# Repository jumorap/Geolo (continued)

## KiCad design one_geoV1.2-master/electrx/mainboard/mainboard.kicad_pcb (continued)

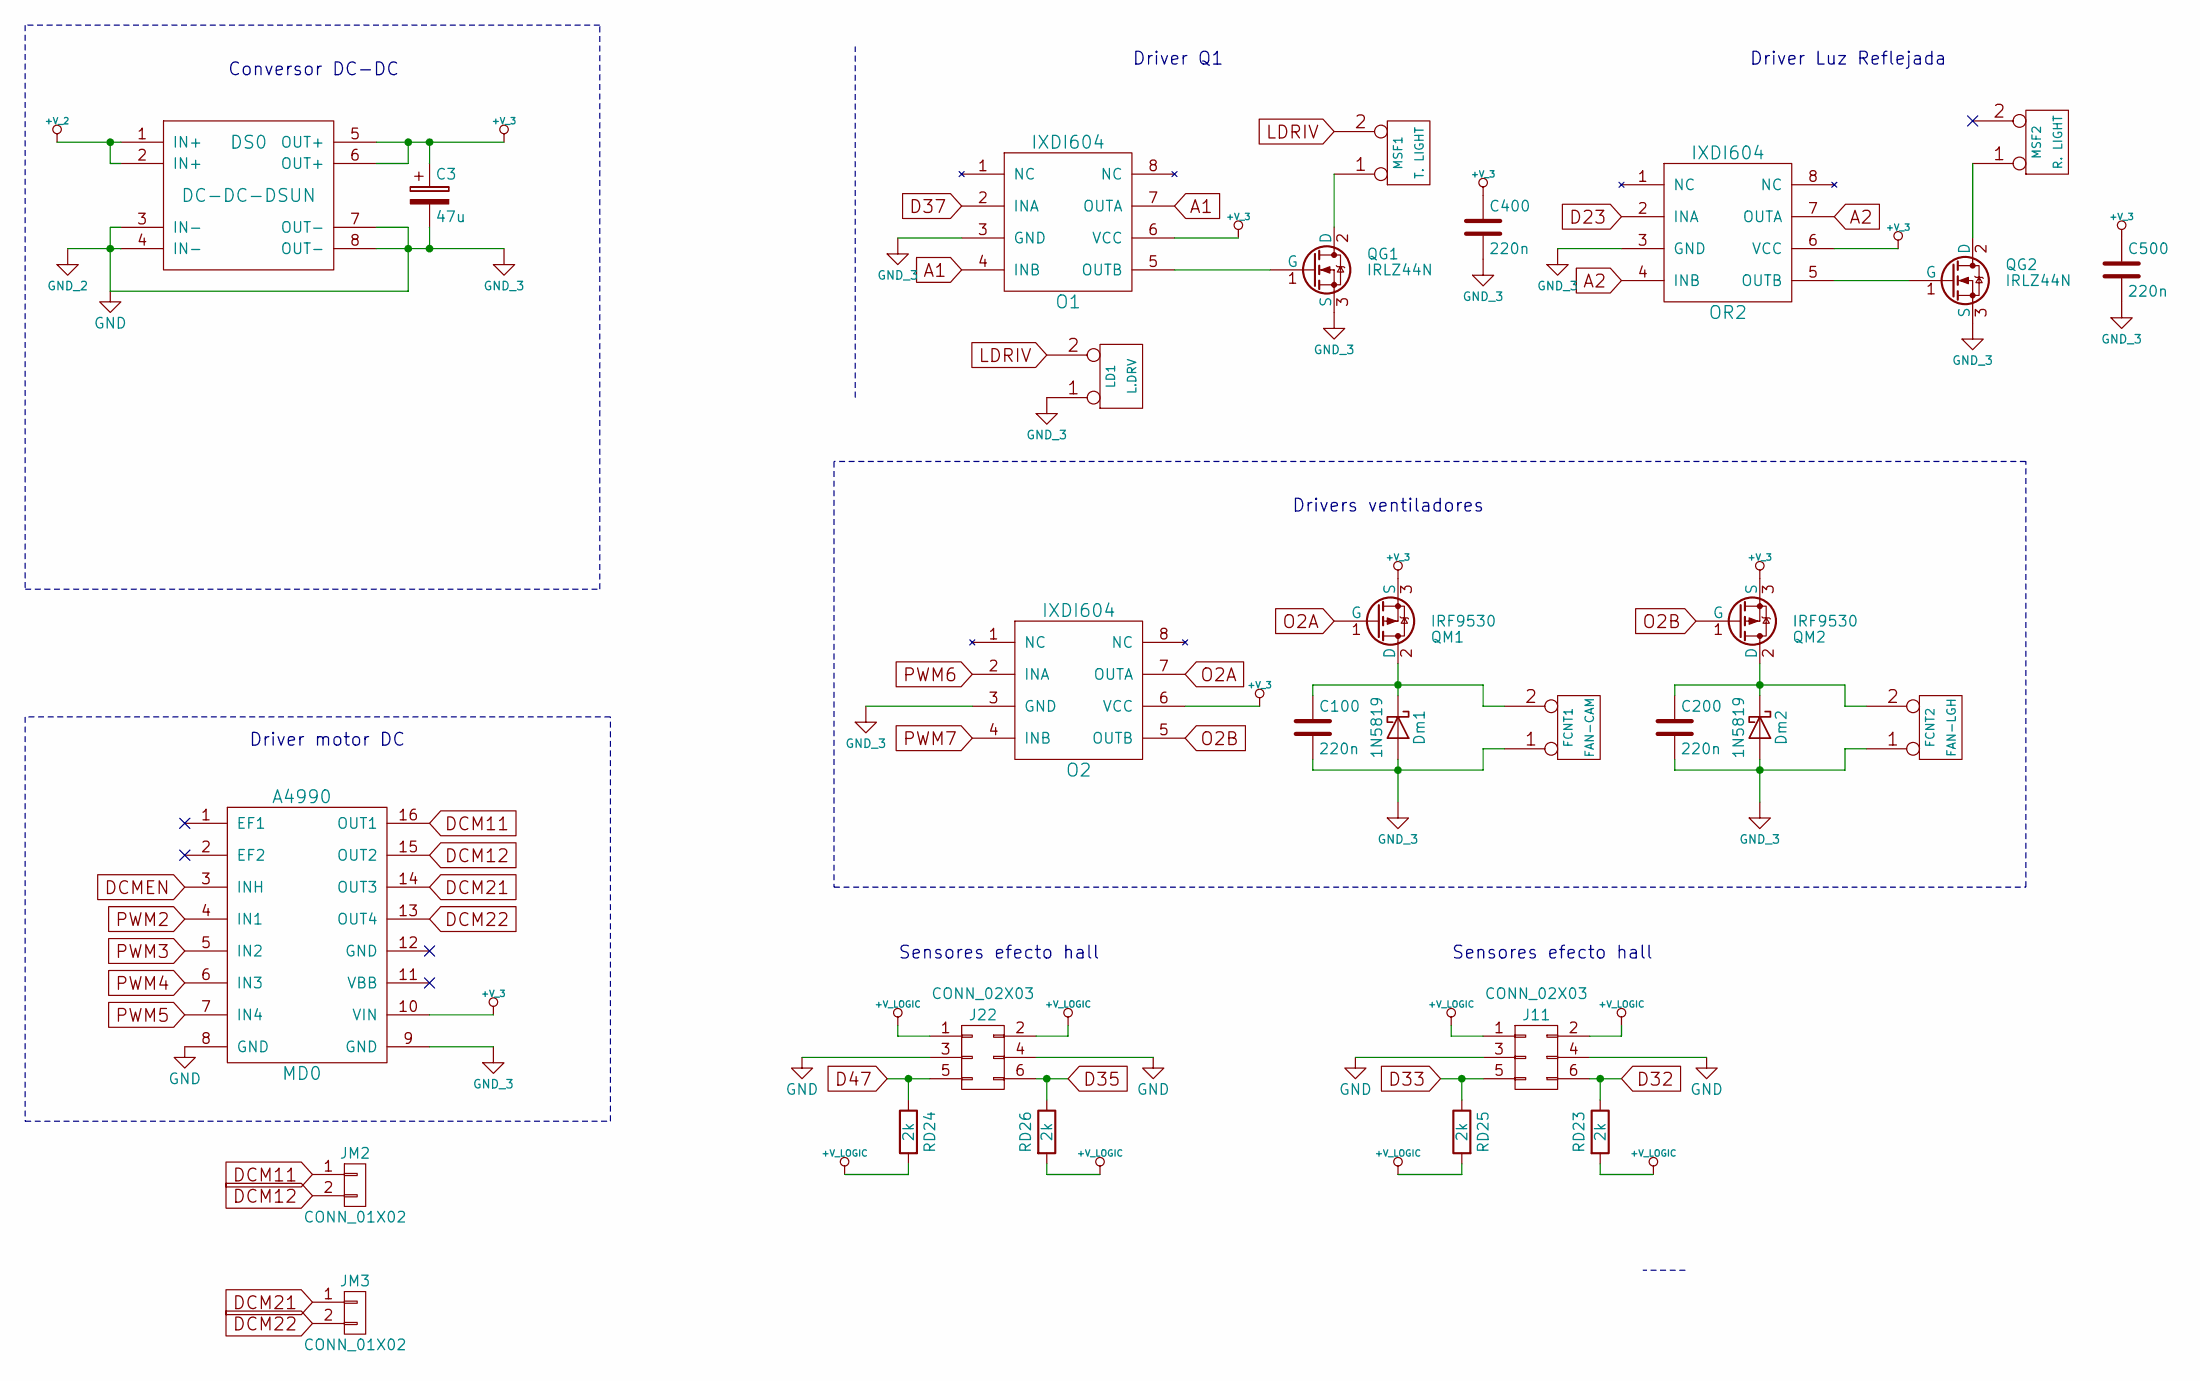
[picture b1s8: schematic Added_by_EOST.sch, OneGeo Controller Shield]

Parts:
C3: 47u; c_elec_5x5.3
C100, C200, C400, C500: 220n; c_0805
DS0: DC-DC-DSUN; D-SUN_DC-DC
Dm1, Dm2: 1N5819; Diode_DO-41_SOD81_Horizontal_RM10
FCNT1: FAN-CAM; mors_2p
FCNT2: FAN-LGH; mors_2p
J11, J22: CONN_02X03; pin_socket_3x2
JM2, JM3: CONN_01X02; pin_strip_2
LD1: L.DRV; mors_2p
MD0: A4990; POLOLU
MSF1: T. LIGHT; mors_2p
MSF2: R. LIGHT; mors_2p
O1, O2: IXDI604; SOIC-8_3.9x4.9mm_Pitch1.27mm
OR2: IXDI604; SOIC-8_3.9x4.9mm_Pitch1.27mm
QG1, QG2: IRLZ44N; TO220_V_RMC
QM1, QM2: IRF9530; TO220_V_RMC
RD23, RD24, RD25, RD26: 2k; SM0805_Opendous

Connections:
+V_2: DS0.1 (IN+), DS0.2 (IN+); also elsewhere on the board
+V_3: C3.1, C400.1, C500.1, DS0.5 (OUT+), DS0.6 (OUT+), MD0.10 (VIN), O1.6 (VCC), O2.6 (VCC), OR2.6 (VCC), QM1.3 (S), QM2.3 (S); also elsewhere on the board
+V_LOGIC: J11.1, J11.2, J22.1, J22.2, RD23.2, RD24.2, RD25.2, RD26.2; also elsewhere on the board
A1: O1.4 (INB), O1.7 (OUTA)
A2: OR2.4 (INB), OR2.7 (OUTA)
D23: OR2.2 (INA); also elsewhere on the board
D32: J11.6, RD23.1; also elsewhere on the board
D33: J11.5, RD25.1; also elsewhere on the board
D35: J22.6, RD26.1; also elsewhere on the board
D37: O1.2 (INA); also elsewhere on the board
D47: J22.5, RD24.1; also elsewhere on the board
DCM11: JM2.1, MD0.16 (OUT1)
DCM12: JM2.2, MD0.15 (OUT2)
DCM21: JM3.1, MD0.14 (OUT3)
DCM22: JM3.2, MD0.13 (OUT4)
DCMEN: MD0.3 (INH); also elsewhere on the board
LDRIV: LD1.2 (PM), MSF1.2 (PM)
MOT_GND: C3.2, C100.2, C200.2, C400.2, C500.2, DS0.3 (IN-), DS0.4 (IN-), DS0.7 (OUT-), DS0.8 (OUT-), Dm1.2 (A), Dm2.2 (A), FCNT1.1, FCNT2.1, J11.3, J11.4, J22.3, J22.4, LD1.1, MD0.8 (GND), MD0.9 (GND), O1.3 (GND), O2.3 (GND), OR2.3 (GND), QG1.3 (S), QG2.3 (S); also elsewhere on the board
unnamed: C100.1, Dm1.1 (K), FCNT1.2 (PM), QM1.2 (D)
unnamed: C200.1, Dm2.1 (K), FCNT2.2 (PM), QM2.2 (D)
unnamed: MSF1.1, QG1.2 (D)
unnamed: MSF2.1, QG2.2 (D)
unnamed: O1.5 (OUTB), QG1.1 (G)
unnamed: OR2.5 (OUTB), QG2.1 (G)
O2A: O2.7 (OUTA), QM1.1 (G)
O2B: O2.5 (OUTB), QM2.1 (G)
PWM2: MD0.4 (IN1); also elsewhere on the board
PWM3: MD0.5 (IN2); also elsewhere on the board
PWM4: MD0.6 (IN3); also elsewhere on the board
PWM5: MD0.7 (IN4); also elsewhere on the board
PWM6: O2.2 (INA); also elsewhere on the board
PWM7: O2.4 (INB); also elsewhere on the board

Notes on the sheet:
Sensores efecto hall
Driver motor DC
Conversor DC-DC
Drivers ventiladores
Driver Q1
Driver Luz Reflejada

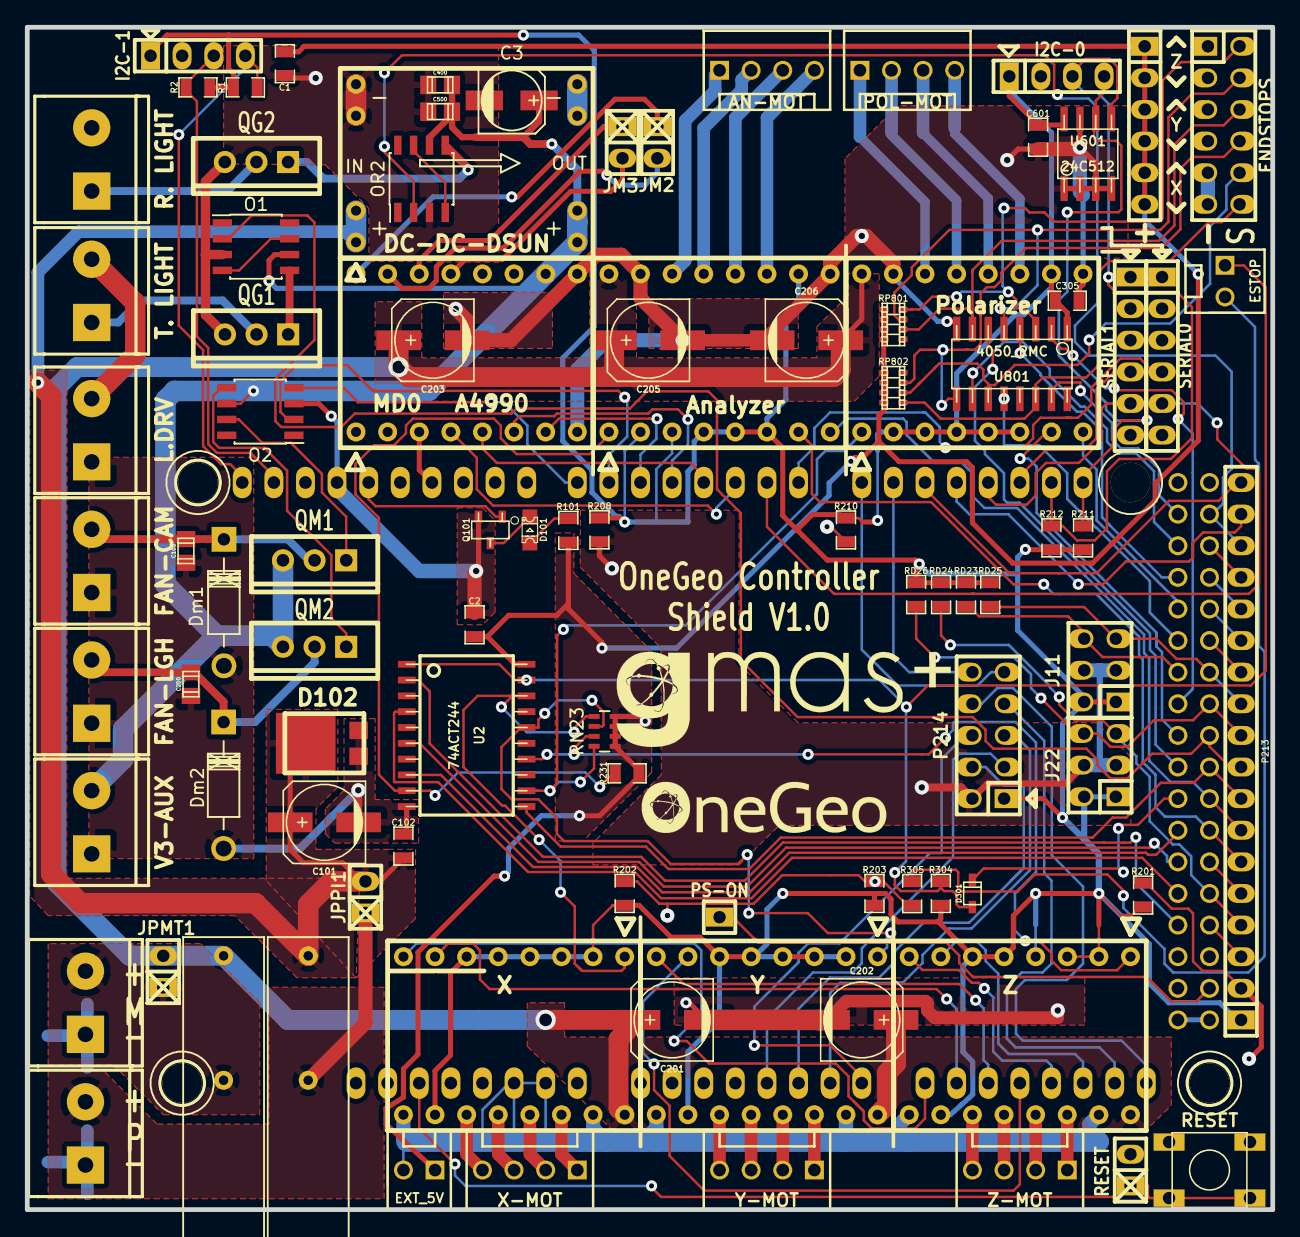
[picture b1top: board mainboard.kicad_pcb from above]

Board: 2 copper layers, 100.1 x 95.0 mm, 95 parts (0 on the bottom side), 121 nets.

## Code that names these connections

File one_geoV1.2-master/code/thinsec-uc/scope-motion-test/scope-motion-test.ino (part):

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#include "PositionEvents.h"

#define NUM_MOTORS  5
AccelStepper mX(AccelStepper::DRIVER, X_STEP_PIN, X_DIR_PIN);
AccelStepper mY(AccelStepper::DRIVER, Y_STEP_PIN, Y_DIR_PIN);
AccelStepper mZ(AccelStepper::DRIVER, Z_STEP_PIN, Z_DIR_PIN);
AccelStepper mP(AccelStepper::DRIVER, E0_STEP_PIN, E0_DIR_PIN);
AccelStepper mA(AccelStepper::DRIVER, E1_STEP_PIN, E1_DIR_PIN);

MotorDataMap motors_map[NUM_MOTORS] = {
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    pinMode(LED2_PIN, OUTPUT);
    pinMode(CAM_TRIGGER_PIN, OUTPUT);

    pinMode(X_STEP_PIN, OUTPUT);
    pinMode(X_DIR_PIN, OUTPUT);
    pinMode(X_ENABLE_PIN, OUTPUT);

    pinMode(Y_STEP_PIN, OUTPUT);
    pinMode(Y_DIR_PIN, OUTPUT);
    pinMode(Y_ENABLE_PIN, OUTPUT);

    pinMode(Z_STEP_PIN, OUTPUT);
    pinMode(Z_DIR_PIN, OUTPUT);
    pinMode(Z_ENABLE_PIN, OUTPUT);

    pinMode(E0_STEP_PIN, OUTPUT);
    pinMode(E0_DIR_PIN, OUTPUT);
    pinMode(E0_ENABLE_PIN, OUTPUT);

    pinMode(E1_STEP_PIN, OUTPUT);
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
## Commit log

2020-01-26 1
    teste_zmqt
2020-01-29 Utils
    -average_images
    -bfield_lin_remove (incompleto)
2020-01-29 Utils
    Organizacion 4 life
2020-01-29 Utils_ 2%
    -crop_get_circle
    -plot_focus_table_common
2020-02-24 Documentation
